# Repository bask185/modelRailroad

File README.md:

# All in one Hardware and Software

# Input, Output System and Interface.

Before I explain the content of this repository it is needed that you understand the concepts of 'input', 'output', 'system', 'communication bus' and 'interface'.

**Input** can be considered as an event with which information can be inserted in a system. Pressing a button on your control panel, turning the knob of your hand controller and a train driving over a feedback track is all considered input.

**Output** is an action. Something which happens. An LED which lights up on your control panel, a point being set, a train departing is all considered output.

A **system** is a coherence of input, output and the way between. A system can exist out of a switch which is directly connected to a point motor with a copper wire, but a system can also consist out of a dcc central and computer.

A system often comprises a **communication bus**. Such a bus is intented to connect more than two devices to. This allows for easier wiring and different manufactories can design their devices to work with such a bus. Examples of communication busses found in our model railways are Loconet, XpressNet and DCC.

An **interface** is a system with which unrelated things can interract with eachother. In human: a DCC decoder for serco motors is an interface which translates DCC signals to the 50Hz square wave which is needed to drive a servo motor.

# What this repository contains for you.
This repository contains board files and software to make the most used accessory decoders and feedback modules which you can find under most model railway layouts.

One fully assembled unit exists out of three components. There is a base board, interface shield and an Arduino Nano. These three componentes are stacked on top of one another.

There are currently seven different base boards for input and ouput and three different interface shields for XpressNet, Loconet and DCC. Not all combinations are possible, to understand why I tell a little bit about these three interfaces.

**XpressNet** is a communication bus and is primarily intented for input devices only such has handcontrollers and switch panels. Via XpressNet one can input instructions to a digital command central which uses these instructions to make your model railway move. Having that said, XpressNet can perfectly be used for output devices. With a little effort you can control servo motors using a multimaus. Due to the nature of XpressNet being input only, there are no XpressNet occupancy detectors. This does not exist within XpressNet. I do want to add that an XpressNet central may broadcast feedback information to all connected slaves, whether the can use this information or not.

**Loconet** is intented for basically everything, input and output. There are loconet switch pilots, loconet boosters and loconet occupancy detectors. This makes this bus the most advanced, future proof and usefull bus.

**DCC** is the most used bus to control digital model trains and accessory decoders with. DCC on it's own is output only. The DCC central can only issue commands and there is no feedback. Therefore there are no DCC switch panels or DCC occupancy detectors. This cannot exist.

The busses are linked to eachother via a central. If you issue a command via the XpressNet bus, this command will be sent on the DCC bus. It is also common for centrals which have both XpressNet and Loconet to translate the instructions and relay the instructions on the other bus. For instance, if you use an XpressNet hand controller and Loconet hand controller, both hand controllers will be aware of eachother's instructions.

I want to add that both Loconet and XpressNet can bus used without a DCC central. You can for instance use the loconet bus to connect a switch panel to servo decoder. Or you can let occupancy detectors automatically control signals and also light up LEDs on your control panel. 
##  Relay
The most simple relay base is ment to easily connect tot the 8 channel or 16 channel relay cards you can find on every electronics webshop. The relay base can be used with all three interfaces.

## Control Panel
The control panel base is ment to connect up to 16 switches to with which you can make a control panel. With such a control panel, you can control all kind of outputs like relays, servos, leds etc. Cannot be used with the DCC interface.

## LED panel
The led panel base is used to control up to 32 LEDs in 16 groups of 2 LEDs. An LED may be used as physical feedback of a state of point or relay. But an LED may also show the state of an occupance detector or not. If you use a group of 2 Leds, one LED will always be opposite to the other LED. Can work with all three interfaces.

## Servo
The servo base can be used to control four servo motors with. This base also has four relays to control frogs of points or make sections of track powerless (usefull for analog layouts). Each base has 2 potentiometers with which one can fine tune the servos' positions individualy. The relays are toggled halveway the servo's movement.  Can work with all three interfaces.

## MOSFET
The mosfet base is designed to drive heavy loads such as magnetic coil operated point motors. It may control up to four double coil which are switched with a pulse. With a different firmware this base may be used to drive 8 coils individualy. Can work with all three interfaces.

## occupancy detector
The occupancy detector can use either current sensing or mass detection. For mass detection you need to use higher value resistors and you don't have to solder all bridge rectifiers and the resistor network. The inputs are all galvanic insulated. This detector can detect up to eight tracks.

Note. With default firmware you must use detector in combination with the loconet bus. It allows you to send occupancy information to a digital central. With the switch panel firmware, you can use this detector to directly control signals and/or LEDs on a control panel.

## Signal
The signal base board can control up to 4 3-tone signals. There are 2 different firmware versions for this base. Signals can be controlled directly by occupancy detectors or switch panel buttons and signals can be controlled by a computer. The signals can use overlapping addresses and become fully automated block signals but for computer operation the signals can also be used with 2 addressed for each signal. Can work with all three interfaces.

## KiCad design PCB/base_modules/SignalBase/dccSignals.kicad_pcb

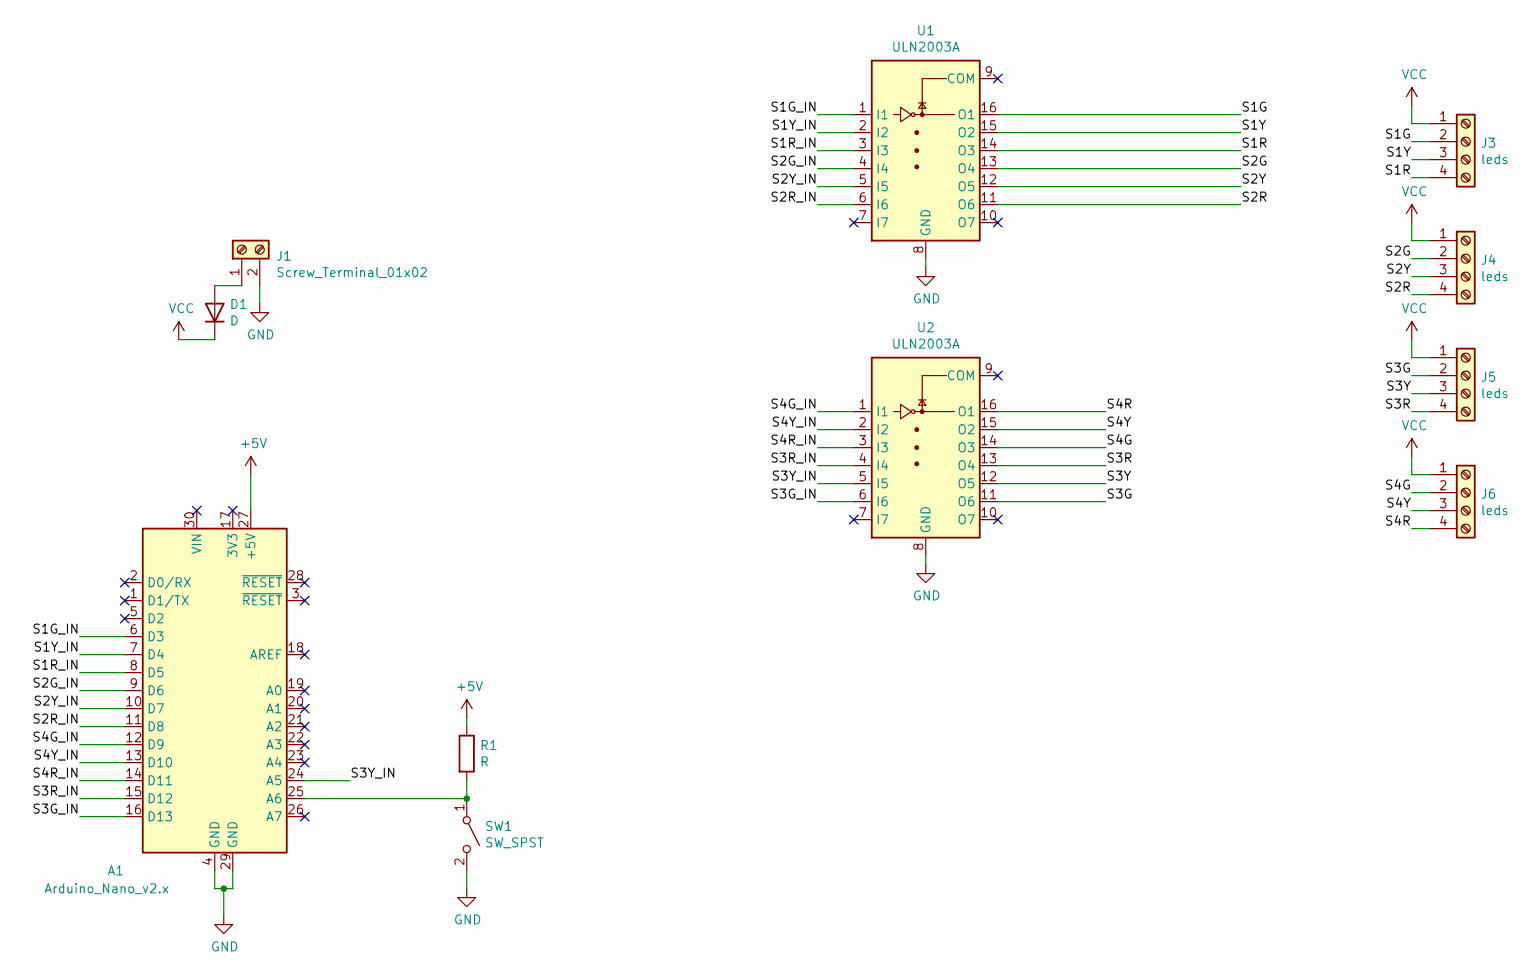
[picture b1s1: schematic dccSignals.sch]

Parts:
A1: Arduino_Nano_v2.x; Arduino_Nano
D1: D; D_DO-34_SOD68_P7.62mm_Horizontal
J1: Screw_Terminal_01x02; TerminalBlock_Phoenix_MKDS-1,5-2-5.08_1x02_P5.08mm_Horizont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
J3, J4, J5, J6: leds; TerminalBlock_Phoenix_MKDS-1,5-4-5.08_1x04_P5.08mm_Horizont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
R1: R; R_Axial_DIN0207_L6.3mm_D2.5mm_P7.62mm_Horizontal
SW1: SW_SPST; SW_PUSH_6mm_H4.3mm
U1, U2: ULN2003A; DIP-16_W7.62mm

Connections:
+5V: A1.27 (+5V), R1.1
/S1G: J3.2, U1.16 (O1)
/S1G_IN: A1.6 (D3), U1.1 (I1)
/S1R: J3.4, U1.14 (O3)
/S1R_IN: A1.8 (D5), U1.3 (I3)
/S1Y: J3.3, U1.15 (O2)
/S1Y_IN: A1.7 (D4), U1.2 (I2)
/S2G: J4.2, U1.13 (O4)
/S2G_IN: A1.9 (D6), U1.4 (I4)
/S2R: J4.4, U1.11 (O6)
/S2R_IN: A1.11 (D8), U1.6 (I6)
/S2Y: J4.3, U1.12 (O5)
/S2Y_IN: A1.10 (D7), U1.5 (I5)
/S3G: J5.2, U2.11 (O6)
/S3G_IN: A1.16 (D13), U2.6 (I6)
/S3R: J5.4, U2.13 (O4)
/S3R_IN: A1.15 (D12), U2.4 (I4)
/S3Y: J5.3, U2.12 (O5)
/S3Y_IN: A1.24 (A5), U2.5 (I5)
/S4G: J6.2, U2.14 (O3)
/S4G_IN: A1.12 (D9), U2.1 (I1)
/S4R: J6.4, U2.16 (O1)
/S4R_IN: A1.14 (D11), U2.3 (I3)
/S4Y: J6.3, U2.15 (O2)
/S4Y_IN: A1.13 (D10), U2.2 (I2)
GND: A1.4 (GND), A1.29 (GND), J1.2, SW1.2 (B), U1.8 (GND), U2.8 (GND)
unnamed: A1.25 (A6), R1.2, SW1.1 (A)
unnamed: D1.2 (A), J1.1
VCC: D1.1 (K), J3.1, J4.1, J5.1, J6.1

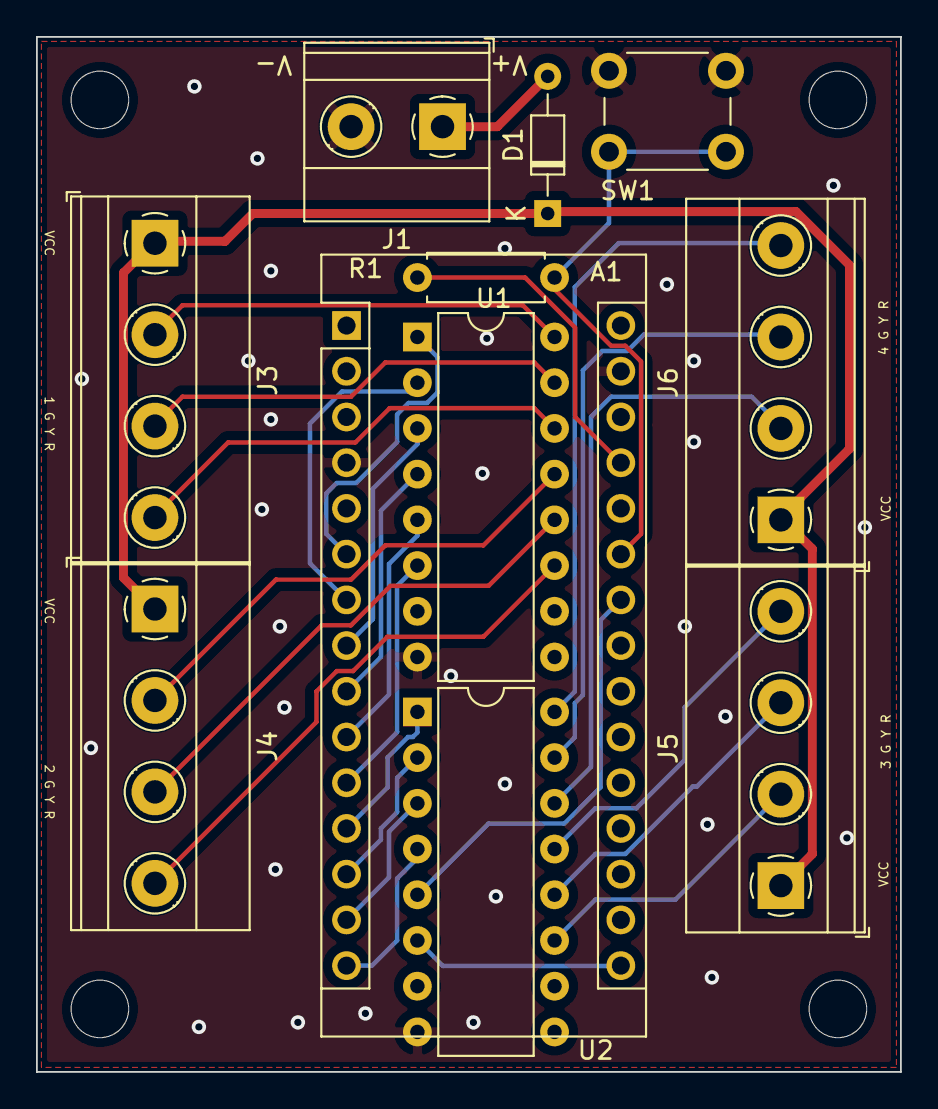
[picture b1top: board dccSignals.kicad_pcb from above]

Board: 2 copper layers, 48.0 x 57.5 mm, 11 parts (0 on the bottom side), 29 nets.

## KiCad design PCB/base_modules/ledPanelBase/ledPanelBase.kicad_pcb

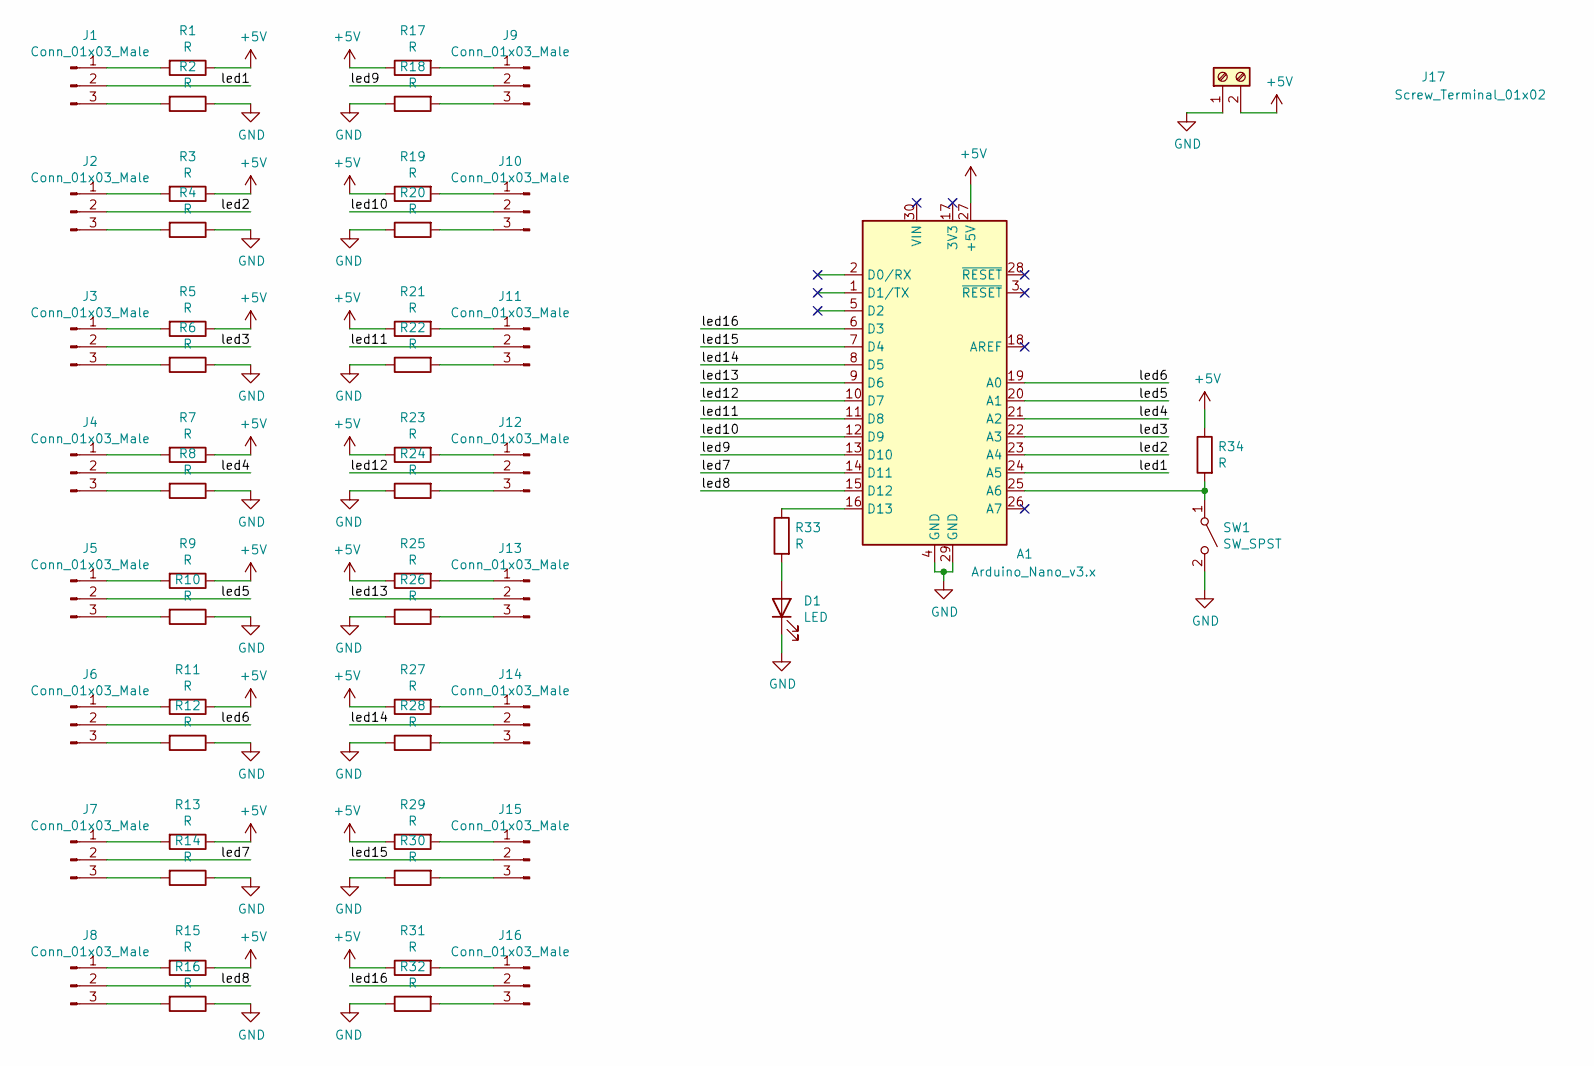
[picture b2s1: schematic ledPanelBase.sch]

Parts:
A1: Arduino_Nano_v3.x; Arduino_Nano
D1: LED; LED_D3.0mm
J1, J2, J3, J4, J5, J6, J7, J8, J9, J10, J11, J12, J13, J14, J15, J16: Conn_01x03_Male; PinHeader_1x03_P2.54mm_Vertical
J17: Screw_Terminal_01x02; TerminalBlock_bornier-2_P5.08mm
R1, R2, R3, R4, R5, R6, R7, R8, R9, R10, R11, R12, R13, R14, R15, R16, R17, R18, R19, R20, R21, R22, R23, R24, R25, R26, R27, R28, R29, R30, R31, R32, R33, R34: R; R_Axial_DIN0204_L3.6mm_D1.6mm_P7.62mm_Horizontal
SW1: SW_SPST; SW_PUSH_6mm_H4.3mm

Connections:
+5V: A1.27 (+5V), J17.2, R1.1, R3.1, R5.1, R7.1, R9.1, R11.1, R13.1, R15.1, R17.1, R19.1, R21.1, R23.1, R25.1, R27.1, R29.1, R31.1, R34.1
/led1: A1.24 (A5), J1.2
/led2: A1.23 (A4), J2.2
/led3: A1.22 (A3), J3.2
/led4: A1.21 (A2), J4.2
/led5: A1.20 (A1), J5.2
/led6: A1.19 (A0), J6.2
/led7: A1.14 (D11), J7.2
/led8: A1.15 (D12), J8.2
/led9: A1.13 (D10), J9.2
/led10: A1.12 (D9), J10.2
/led11: A1.11 (D8), J11.2
/led12: A1.10 (D7), J12.2
/led13: A1.9 (D6), J13.2
/led14: A1.8 (D5), J14.2
/led15: A1.7 (D4), J15.2
/led16: A1.6 (D3), J16.2
GND: A1.4 (GND), A1.29 (GND), D1.1 (K), J17.1, R2.1, R4.1, R6.1, R8.1, R10.1, R12.1, R14.1, R16.1, R18.1, R20.1, R22.1, R24.1, R26.1, R28.1, R30.1, R32.1, SW1.2 (B)
unnamed: A1.16 (D13), R33.1
unnamed: A1.25 (A6), R34.2, SW1.1 (A)
unnamed: D1.2 (A), R33.2
unnamed: J1.1, R1.2
unnamed: J1.3, R2.2
unnamed: J2.1, R3.2
unnamed: J2.3, R4.2
unnamed: J3.1, R5.2
unnamed: J3.3, R6.2
unnamed: J4.1, R7.2
unnamed: J4.3, R8.2
unnamed: J5.1, R9.2
unnamed: J5.3, R10.2
unnamed: J6.1, R11.2
unnamed: J6.3, R12.2
unnamed: J7.1, R13.2
unnamed: J7.3, R14.2
unnamed: J8.1, R15.2
unnamed: J8.3, R16.2
unnamed: J9.1, R17.2
unnamed: J9.3, R18.2
unnamed: J10.1, R19.2
unnamed: J10.3, R20.2
unnamed: J11.1, R21.2
unnamed: J11.3, R22.2
unnamed: J12.1, R23.2
unnamed: J12.3, R24.2
unnamed: J13.1, R25.2
unnamed: J13.3, R26.2
unnamed: J14.1, R27.2
unnamed: J14.3, R28.2
unnamed: J15.1, R29.2
unnamed: J15.3, R30.2
unnamed: J16.1, R31.2
unnamed: J16.3, R32.2

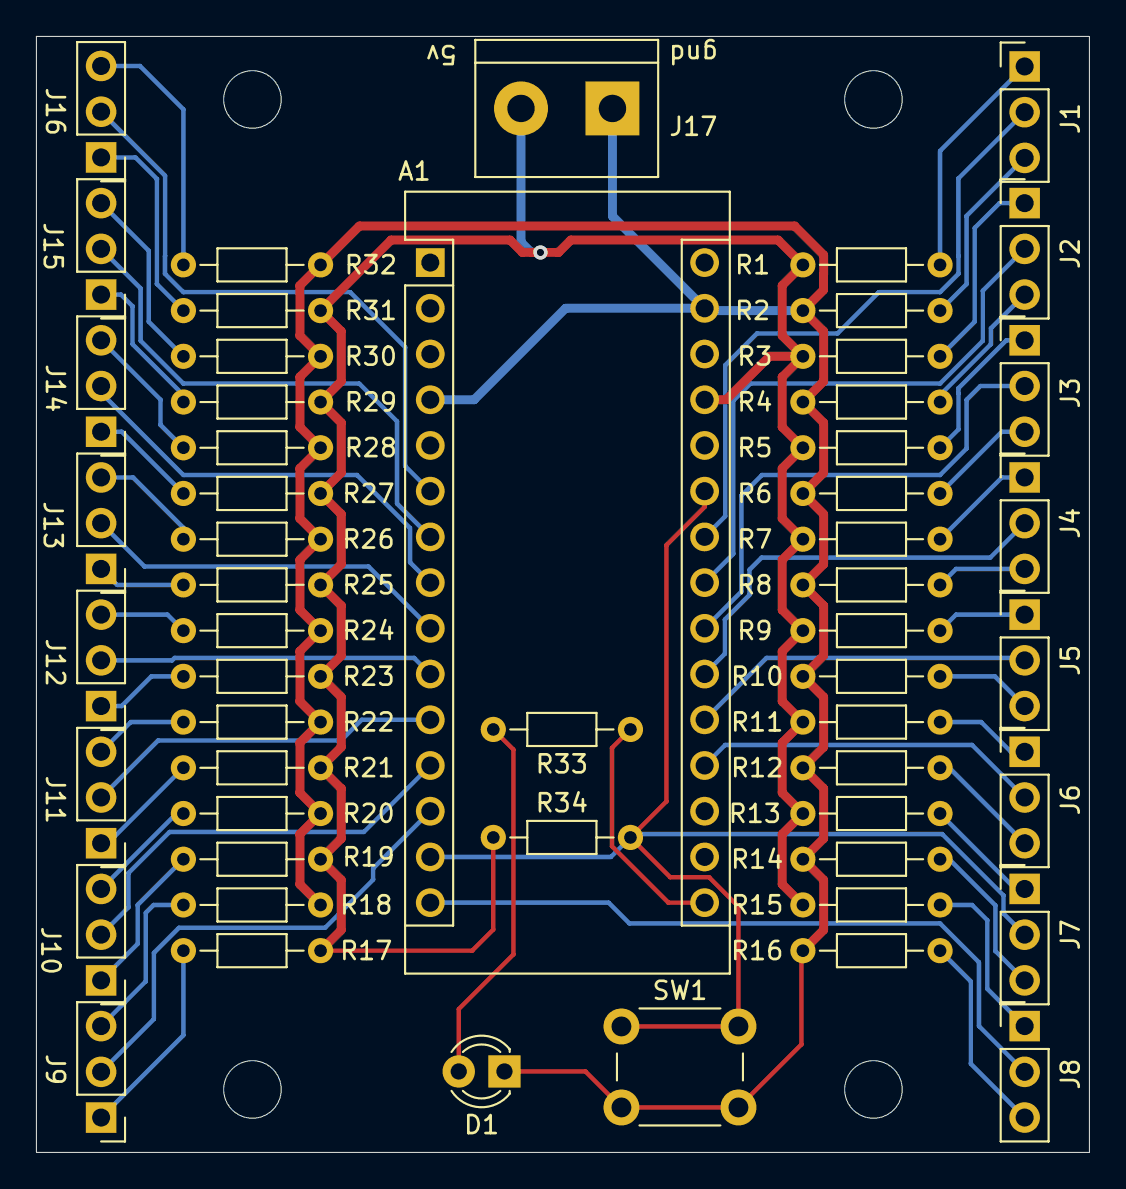
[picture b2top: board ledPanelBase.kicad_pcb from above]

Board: 2 copper layers, 58.5 x 62.0 mm, 54 parts (0 on the bottom side), 53 nets.

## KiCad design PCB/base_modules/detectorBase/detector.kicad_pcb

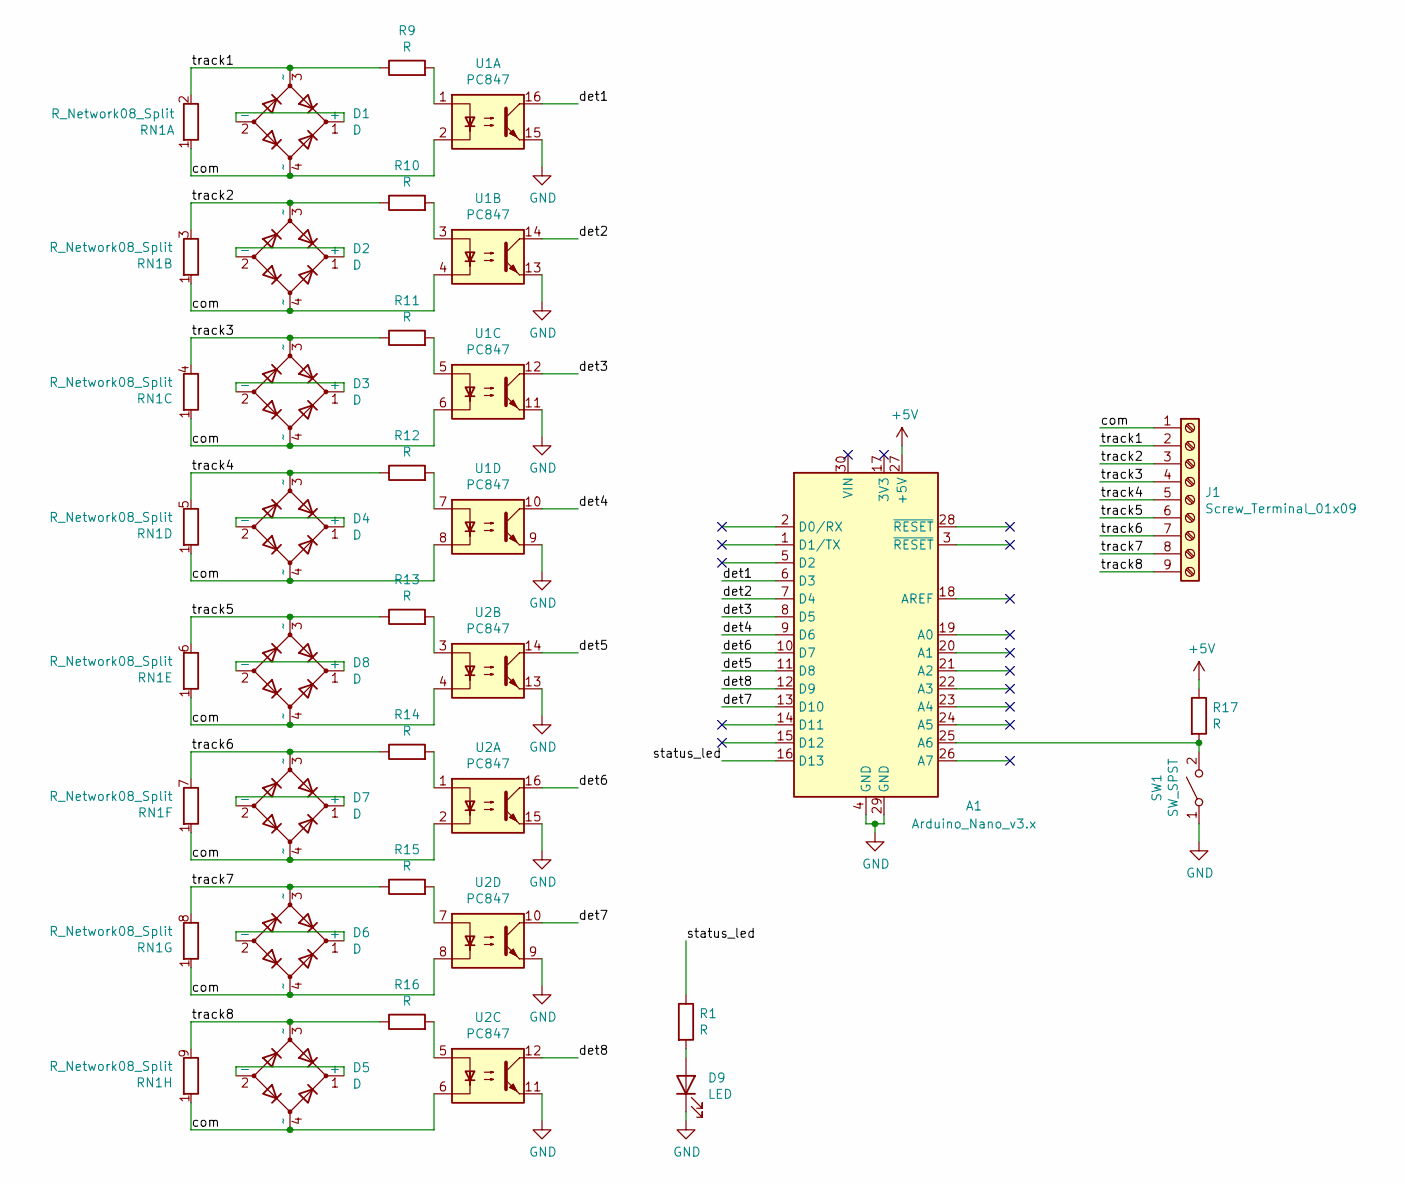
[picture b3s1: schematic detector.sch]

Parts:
A1: Arduino_Nano_v3.x; Arduino_Nano
D1, D2, D3, D4, D5, D6, D7, D8: D; Diode_Bridge_DIP-4_W7.62mm_P5.08mm
D9: LED; LED_D3.0mm
J1: Screw_Terminal_01x09; TerminalBlock_Phoenix_MKDS-1,5-9-5.08_1x09_P5.08mm_Horizont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
R1, R9, R10, R11, R12, R13, R14, R15, R16, R17: R; R_Axial_DIN0204_L3.6mm_D1.6mm_P7.62mm_Horizontal
RN1: R_Network08_Split; R_Array_SIP9
SW1: SW_SPST; SW_PUSH_6mm_H4.3mm
U1, U2: PC847; DIP-16_W7.62mm

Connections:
+5V: A1.27 (+5V), R17.1
/com: D1.4 (~~), D2.4 (~~), D3.4 (~~), D4.4 (~~), D5.4 (~~), D6.4 (~~), D7.4 (~~), D8.4 (~~), J1.1, RN1.1 (R1.1), U1.2, U1.4, U1.6, U1.8, U2.2, U2.4, U2.6, U2.8
/det1: A1.6 (D3), U1.16
/det2: A1.7 (D4), U1.14
/det3: A1.8 (D5), U1.12
/det4: A1.9 (D6), U1.10
/det5: A1.11 (D8), U2.14
/det6: A1.10 (D7), U2.16
/det7: A1.13 (D10), U2.10
/det8: A1.12 (D9), U2.12
/status_led: A1.16 (D13), R1.1
/track1: D1.3 (~~), J1.2, R9.1, RN1.2 (R1.2)
/track2: D2.3 (~~), J1.3, R10.1, RN1.3 (R2.2)
/track3: D3.3 (~~), J1.4, R11.1, RN1.4 (R3.2)
/track4: D4.3 (~~), J1.5, R12.1, RN1.5 (R4.2)
/track5: D8.3 (~~), J1.6, R13.1, RN1.6 (R5.2)
/track6: D7.3 (~~), J1.7, R14.1, RN1.7 (R6.2)
/track7: D6.3 (~~), J1.8, R15.1, RN1.8 (R7.2)
/track8: D5.3 (~~), J1.9, R16.1, RN1.9 (R8.2)
GND: A1.4 (GND), A1.29 (GND), D9.1 (K), SW1.1 (A), U1.9, U1.11, U1.13, U1.15, U2.9, U2.11, U2.13, U2.15
unnamed: A1.25 (A6), R17.2, SW1.2 (B)
unnamed: D1.1 (+), D1.2 (-)
unnamed: D2.1 (+), D2.2 (-)
unnamed: D3.1 (+), D3.2 (-)
unnamed: D4.1 (+), D4.2 (-)
unnamed: D5.1 (+), D5.2 (-)
unnamed: D6.1 (+), D6.2 (-)
unnamed: D7.1 (+), D7.2 (-)
unnamed: D8.1 (+), D8.2 (-)
unnamed: D9.2 (A), R1.2
unnamed: R9.2, U1.1
unnamed: R10.2, U1.3
unnamed: R11.2, U1.5
unnamed: R12.2, U1.7
unnamed: R13.2, U2.3
unnamed: R14.2, U2.1
unnamed: R15.2, U2.7
unnamed: R16.2, U2.5

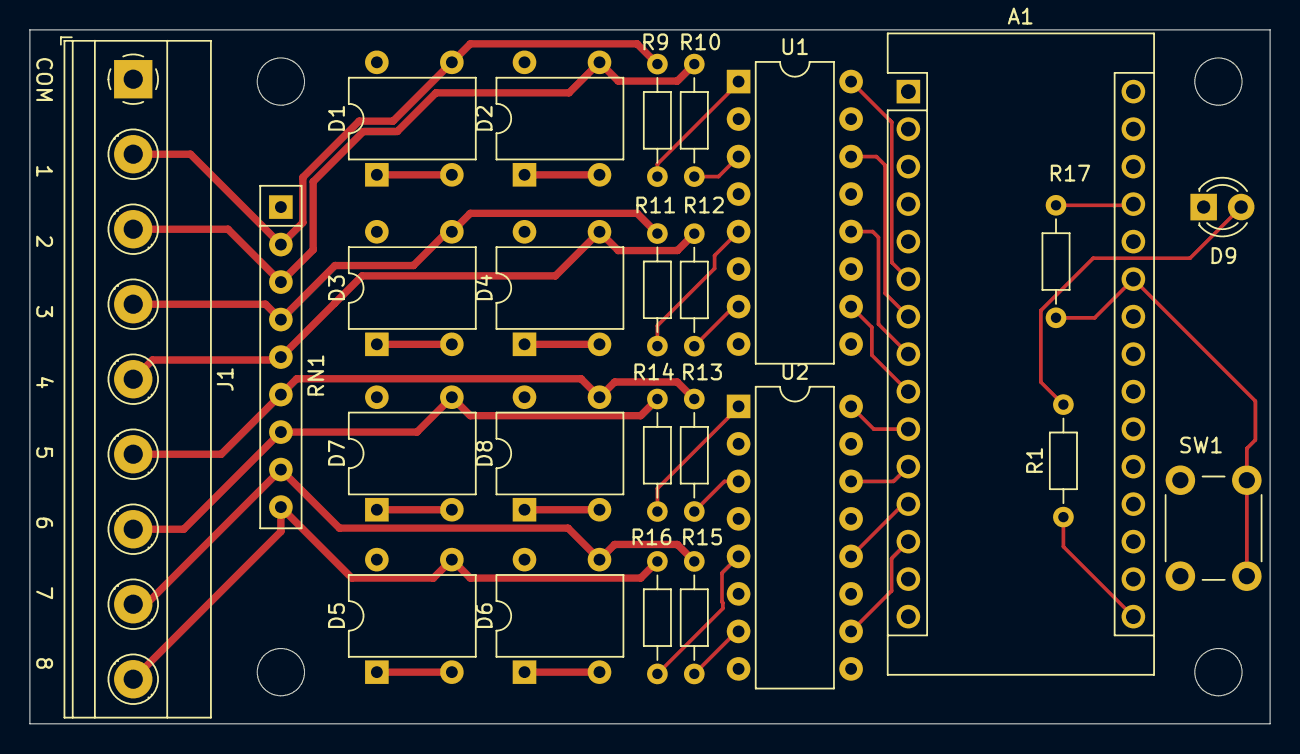
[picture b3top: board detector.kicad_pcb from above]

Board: 2 copper layers, 84.0 x 47.0 mm, 25 parts (0 on the bottom side), 38 nets.

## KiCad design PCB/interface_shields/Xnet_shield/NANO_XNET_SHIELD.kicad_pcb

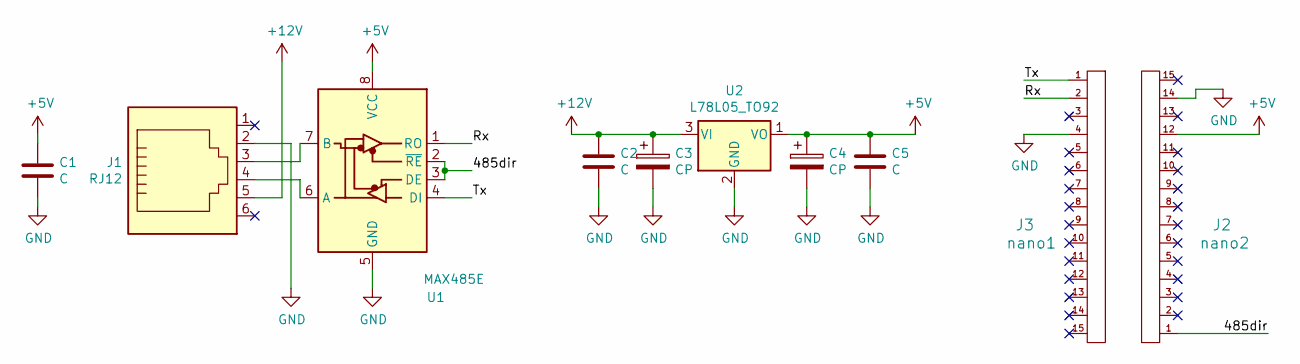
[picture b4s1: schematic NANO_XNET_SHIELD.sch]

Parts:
C1, C2, C5: C; C_Disc_D3.0mm_W1.6mm_P2.50mm
C3, C4: CP; CP_Radial_D4.0mm_P1.50mm
J1: RJ12; RJ25_Wayconn_MJEA-660X1_Horizontal
J2: nano2; PinSocket_1x15_P2.54mm_Vertical
J3: nano1; PinSocket_1x15_P2.54mm_Vertical
U1: MAX485E; DIP-8_W7.62mm
U2: L78L05_TO92; TO-92_Inline

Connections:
+5V: C1.1, C4.1, C5.1, J2.12, U1.8 (VCC), U2.1 (VO)
+12V: C2.1, C3.1, J1.5, U2.3 (VI)
/485dir: J2.1, U1.2 (~RE), U1.3 (DE)
/Rx: J3.2, U1.1 (RO)
/Tx: J3.1, U1.4 (DI)
GND: C1.2, C2.2, C3.2, C4.2, C5.2, J1.2, J2.14, J3.4, U1.5 (GND), U2.2 (GND)
unnamed: J1.3, U1.7 (B)
unnamed: J1.4, U1.6 (A)

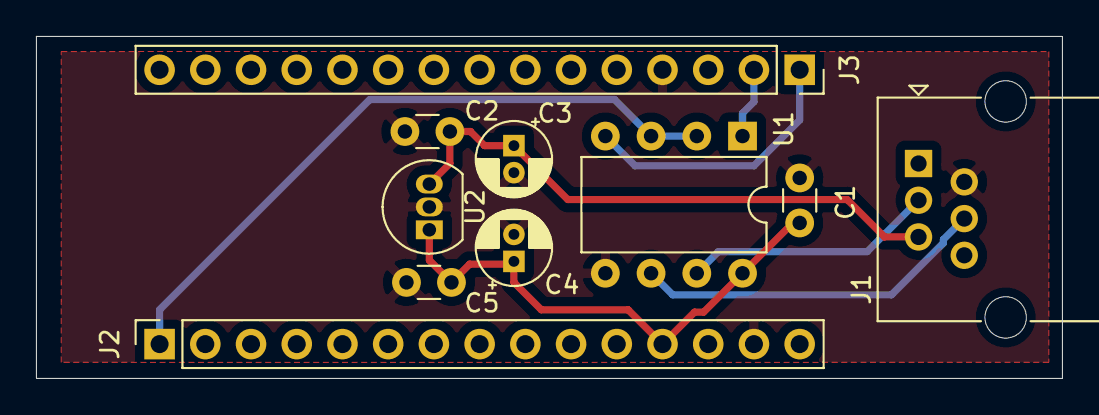
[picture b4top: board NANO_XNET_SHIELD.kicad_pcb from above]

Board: 2 copper layers, 57.0 x 19.0 mm, 10 parts (0 on the bottom side), 8 nets.

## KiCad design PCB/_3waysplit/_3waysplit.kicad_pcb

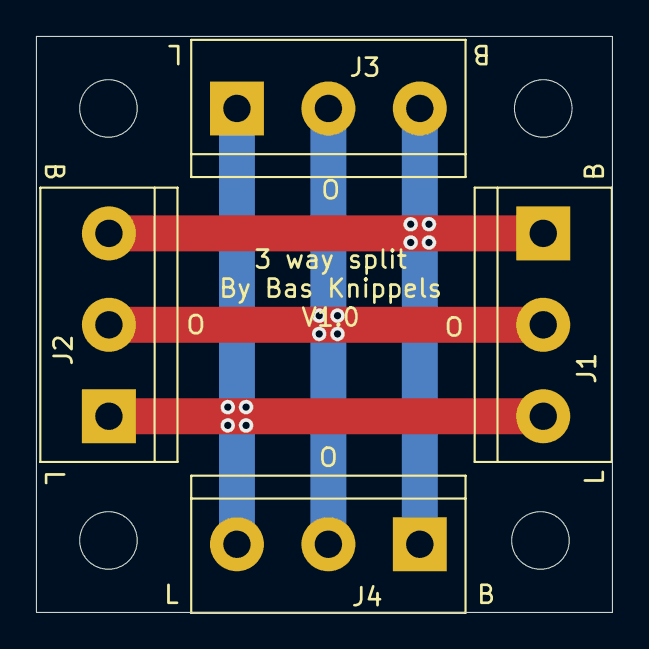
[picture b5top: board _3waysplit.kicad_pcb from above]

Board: 2 copper layers, 32.0 x 32.0 mm, 4 parts (0 on the bottom side), 3 nets.

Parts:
J1, J2, J3, J4: Screw_Terminal_01x03; TerminalBlock_bornier-3_P5.08mm

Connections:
unnamed: J1.1, J2.3, J3.3, J4.1
unnamed: J1.2, J2.2, J3.2, J4.2
unnamed: J1.3, J2.1, J3.1, J4.3

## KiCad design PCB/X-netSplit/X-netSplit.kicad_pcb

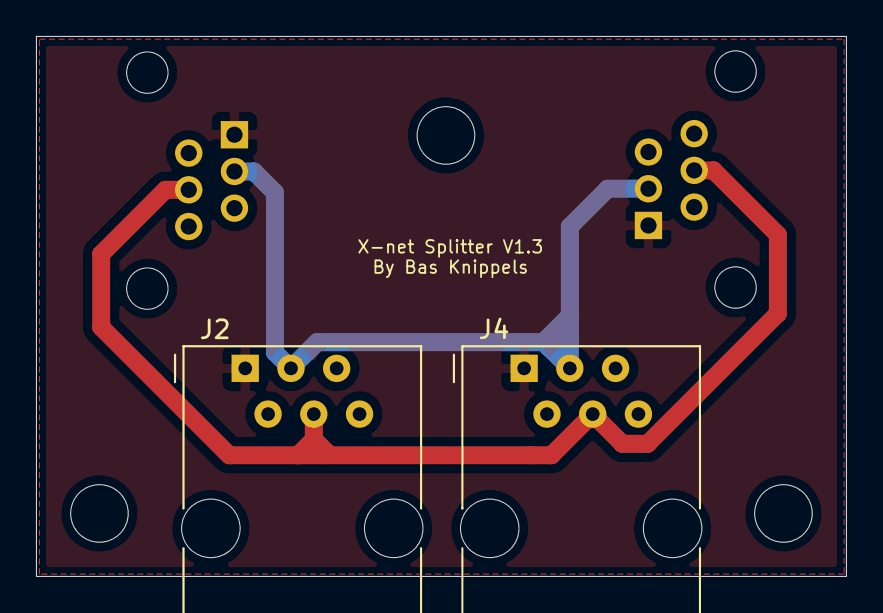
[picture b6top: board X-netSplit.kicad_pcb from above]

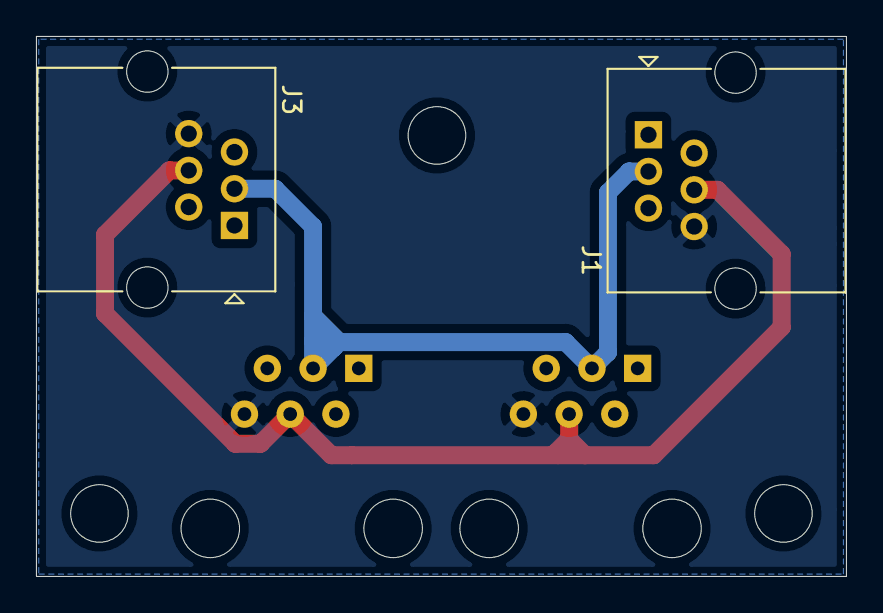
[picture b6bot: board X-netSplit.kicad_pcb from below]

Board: 4 copper layers, 45.0 x 30.0 mm, 4 parts (2 on the bottom side), 6 nets.

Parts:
J1, J3: RJ12; RJ25_Wayconn_MJEA-660X1_Horizontal
J2, J4: RJ12; RJ12_Amphenol_54601

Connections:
unnamed: J1.1, J2.1, J3.1, J4.1
unnamed: J1.2, J2.2, J3.2, J4.2
unnamed: J1.3, J2.3, J3.3, J4.3
unnamed: J1.4, J2.4, J3.4, J4.4
unnamed: J1.5, J2.5, J3.5, J4.5
unnamed: J1.6, J2.6, J3.6, J4.6

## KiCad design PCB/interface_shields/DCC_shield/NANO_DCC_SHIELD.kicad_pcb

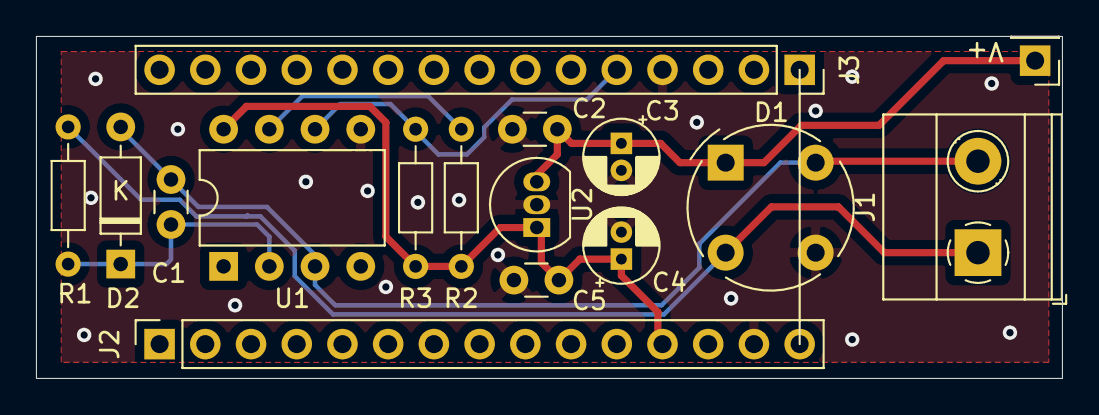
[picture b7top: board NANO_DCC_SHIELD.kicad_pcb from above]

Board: 2 copper layers, 57.0 x 19.0 mm, 16 parts (0 on the bottom side), 8 nets.

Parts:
C1, C2, C5: C; C_Disc_D3.0mm_W1.6mm_P2.50mm
C3, C4: CP; CP_Radial_D4.0mm_P1.50mm
D1: D; Diode_Bridge_Round_D9.0mm
D2: 1N4148; D_DO-35_SOD27_P7.62mm_Horizontal
J1: Screw_Terminal_01x02; TerminalBlock_Phoenix_MKDS-1,5-2-5.08_1x02_P5.08mm_Horizont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
J2: nano2; PinSocket_1x15_P2.54mm_Vertical
J3: nano1; PinSocket_1x15_P2.54mm_Vertical
R1: 1k; R_Axial_DIN0204_L3.6mm_D1.6mm_P7.62mm_Horizontal
R2: 10k; R_Axial_DIN0204_L3.6mm_D1.6mm_P7.62mm_Horizontal
R3: 5k; R_Axial_DIN0204_L3.6mm_D1.6mm_P7.62mm_Horizontal
U1: 6N137; DIP-8_W7.62mm
U2: L78L05_TO92; TO-92_Inline
V+: Conn_01x01_Male; PinHeader_1x01_P2.54mm_Vertical

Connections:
+5V: C4.1, C5.1, J2.12, R2.1, R3.1, U1.8, U2.1
+12V: C2.1, C3.1, D1.1, U2.3, V+.1
/DCC+: D1.2, J1.1, R1.2
/DCC-: C1.2, D1.4, D2.2, J1.2, U1.3
/DCC_IN: J3.5, R3.2, U1.6
GND: C2.2, C3.2, C4.2, C5.2, D1.3, J2.14, J3.4, U1.5, U2.2
unnamed: C1.1, D2.1, R1.1, U1.2
unnamed: R2.2, U1.7

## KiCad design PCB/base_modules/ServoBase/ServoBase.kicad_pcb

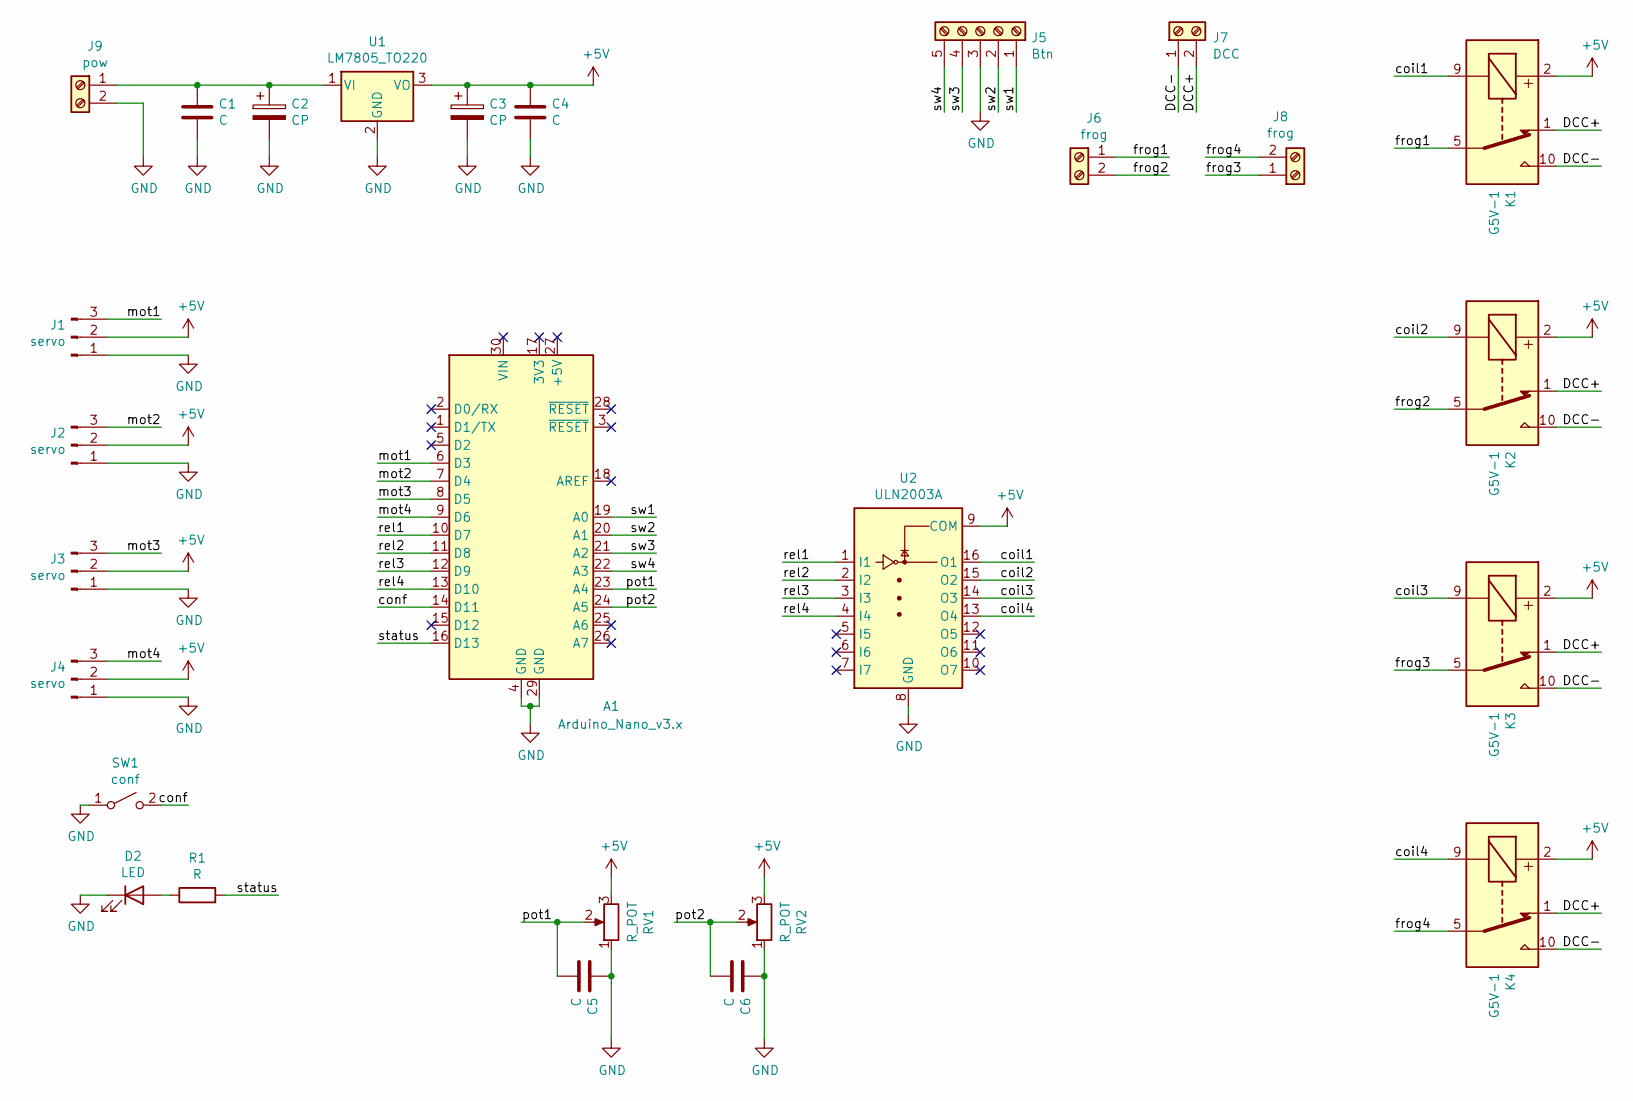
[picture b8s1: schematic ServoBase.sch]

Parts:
A1: Arduino_Nano_v3.x; Arduino_Nano
C1, C4, C5, C6: C; C_Disc_D3.0mm_W1.6mm_P2.50mm
C2, C3: CP; CP_Radial_D7.5mm_P2.50mm
D2: LED; LED_D3.0mm
J1, J2, J3, J4: servo; PinHeader_1x03_P2.54mm_Vertical
J5: Btn; TerminalBlock_Phoenix_MKDS-1,5-5-5.08_1x05_P5.08mm_Horizont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
J6, J8: frog; TerminalBlock_Phoenix_MKDS-1,5-2-5.08_1x02_P5.08mm_Horizont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
J7: DCC; TerminalBlock_Phoenix_MKDS-1,5-2-5.08_1x02_P5.08mm_Horizont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
J9: pow; TerminalBlock_Phoenix_MKDS-1,5-2-5.08_1x02_P5.08mm_Horizont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
K1, K2, K3, K4: G5V-1; Relay_SPDT_Omron_G5V-1
R1: R; R_Axial_DIN0204_L3.6mm_D1.6mm_P7.62mm_Horizontal
RV1, RV2: R_POT; Potentiometer_Runtron_RM-065_Vertical
SW1: conf; SW_PUSH_6mm_H4.3mm
U1: LM7805_TO220; TO-220-3_Vertical
U2: ULN2003A; DIP-16_W7.62mm

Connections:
+5V: C3.1, C4.1, J1.2, J2.2, J3.2, J4.2, K1.2, K2.2, K3.2, K4.2, RV1.3, RV2.3, U1.3 (VO), U2.9 (COM); also elsewhere on the board
/DCC+: J7.2, K1.1, K2.1, K3.1, K4.1
/DCC-: J7.1, K1.10, K2.10, K3.10, K4.10
/coil1: K1.9, U2.16 (O1)
/coil2: K2.9, U2.15 (O2)
/coil3: K3.9, U2.14 (O3)
/coil4: K4.9, U2.13 (O4)
/frog1: J6.1, K1.5, K1.6
/frog2: J6.2, K2.5, K2.6
/frog3: J8.1, K3.5, K3.6
/frog4: J8.2, K4.5, K4.6
/mot1: A1.6 (D3), J1.3
/mot2: A1.7 (D4), J2.3
/mot3: A1.8 (D5), J3.3
/mot4: A1.9 (D6), J4.3
/pot1: A1.23 (A4), C5.2, RV1.2
/pot2: A1.24 (A5), C6.2, RV2.2
/rel1: A1.10 (D7), U2.1 (I1)
/rel2: A1.11 (D8), U2.2 (I2)
/rel3: A1.12 (D9), U2.3 (I3)
/rel4: A1.13 (D10), U2.4 (I4)
/status: A1.16 (D13), R1.2
/sw1: A1.19 (A0), J5.1
/sw2: A1.20 (A1), J5.2
/sw3: A1.21 (A2), J5.4
/sw4: A1.22 (A3), J5.5
GND: A1.4 (GND), A1.29 (GND), C1.2, C2.2, C3.2, C4.2, C5.1, C6.1, D2.1 (K), J1.1, J2.1, J3.1, J4.1, J5.3, J9.2, RV1.1, RV2.1, SW1.1 (A), U1.2 (GND), U2.8 (GND)
unnamed: C1.1, C2.1, J9.1, U1.1 (VI)
unnamed: D2.2 (A), R1.1

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
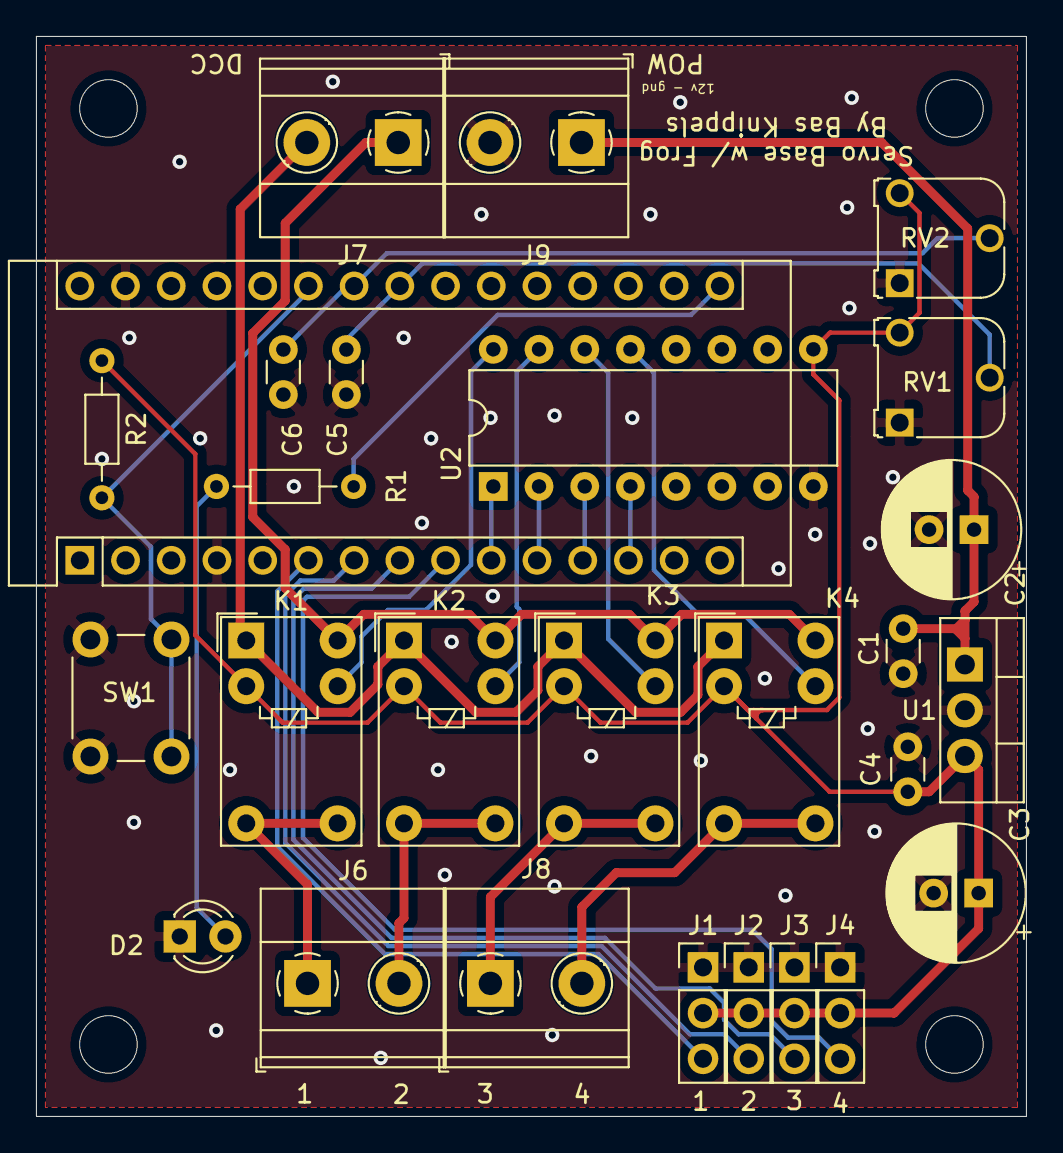
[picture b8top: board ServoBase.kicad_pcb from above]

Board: 2 copper layers, 55.0 x 60.0 mm, 27 parts (0 on the bottom side), 26 nets.

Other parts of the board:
R2: R; R_Axial_DIN0204_L3.6mm_D1.6mm_P7.62mm_Horizontal

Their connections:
+5V: R2.1; also elsewhere on the board
